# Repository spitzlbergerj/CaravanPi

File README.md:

# CaravanPi

ACHTUNG: Dokumentation nicht aktuell v2.0 noch nicht eingearbeitet

- [Website](https://www.CaravanPi.de)
- [Wiki](https://github.com/spitzlbergerj/CaravanPi/wiki/)
- [Platine bestellen](https://www.caravanpi.de/platine)

- [Newsletter abonnieren (Sendinblue/Brevo Plattform)](https://40fb016c.sibforms.com/serve/MUIFAH4-cq2k2-T8acJ-A43b4eFEC9NdXuY4Qsx0Z8AVap96J-xUTzrsRBFXvzXRIEBnFebbvgbXibn9NFGg8v5Qx55c4hzOQlpmxT23eU7bOGsW2ycUFhNx8PIrJcuGtE8EaE4Ah49gLuzYuZXHCerz-JhMHt5MQxiBJ0xqzuM7EOsEn82apHaTXQg5AoC__NkGssehrymHcnL7)

- [Movitation](#motivation)

## Aktualisierungen / Change Log

Details siehe / Please view [CHANGELOG.md](https://github.com/spitzlbergerj/CaravanPi/blob/master/CHANGELOG.md)

## Motivation

System zur Messung und Anzeige verschiedener Sensorenwerte in Wohnwagen, Caravans und Wohnmobilen, wie z.B. Klimawerte, Füllstände von Tanks und Gasflaschen sowie Nivellierungsdaten. Zur Darstellung wird die Software <a href="https://magicmirror.builders/">Magic Mirror</a> verwendet. 
Es existiert eine Schritt für Schritt Anleitung in deutsch. Englische Schnipsel sind bereits vorhanden und werden ausgebaut werden.
[direkt zur Anleitung](https://github.com/spitzlbergerj/CaravanPi/wiki/Home/)

Schemazeichnung | MagicMirror Anzeige (vor Grafana)
----- | -----
 | 
[größeres Bild](https://github.com/spitzlbergerj/CaravanPi/raw/master/images/CaravanPi.jpg) | [größeres Bild](https://github.com/spitzlbergerj/CaravanPi/raw/master/images/CaravanPi-MagicMirror.jpg) 

## Platinen Design

Die Platine liegt inzwischen in der version V6 vor in die wiederum eine Reihe von Verbesserungen eingeflossen sind.  
Vorderseite | Rückseite
----- | -----
 |  
Alle zum Bestellen der Platine benötigten Angaben und Dateien befinden sich im Verzeichnis circuit-board
Die Platine ist aus SMD Bauteilen aufgebaut. Als Klemmen verwendete ich früher WAGO Klemmen. Aufgrund des hohen Preises derselben bin ich inzwischen auf JST XA Stecker umgestiegen, die auch sehr viel flexibler beim Umbau sind. Bitte auf hochwertige Stecker achten, am besten original JST bauteile verwenden.
Ich kläre gerade mit JLCPCB, bei denen ich meine Platinen bestelle, ob diese Klemmen ebenfalls ab Werk aufgelötet werden können.

Ich habe beinahe immer einige Platinen vorrätig. Bitte nutzen Sie den Bestelllink oben, falls Sie Interesse an einer Platine haben.

## Dokumentation

Die Dokumentation findet im [Wiki](https://github.com/spitzlbergerj/CaravanPi/wiki/) statt. Dieses wird gerade neu aufgebaut, um auch alle neuen Funktionälitäten darstellen zu können.

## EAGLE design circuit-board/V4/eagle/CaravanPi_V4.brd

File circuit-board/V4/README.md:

# Platine Version 4

Diese Platinen Version nutzt SMD Bauteile für alle Widerstände, Kondensatoren, Dioden und ICs inkl. P82B715P I2C Extender Chips. Damit kann diese Platinenversion z. B. bei JLCPCB vollständig gefertigt werden, so dass nur noch Stecker und Klemmen manuell gelötet werden müssen.

## Platinen Layout
Oberseite  

Unterseite  

Bestückungslayout  

Bohrungen  

## JLCPCB Platine maschinell bestückt

Alle für die Bestellung bei JLCPCB.com benötigten dateien finden Sie im Unterverzeichnis [JLCPCB](JLCPCB)

## Bauteile Liste
In der Exceltabelle finden Sie alle benötigten Bauteile

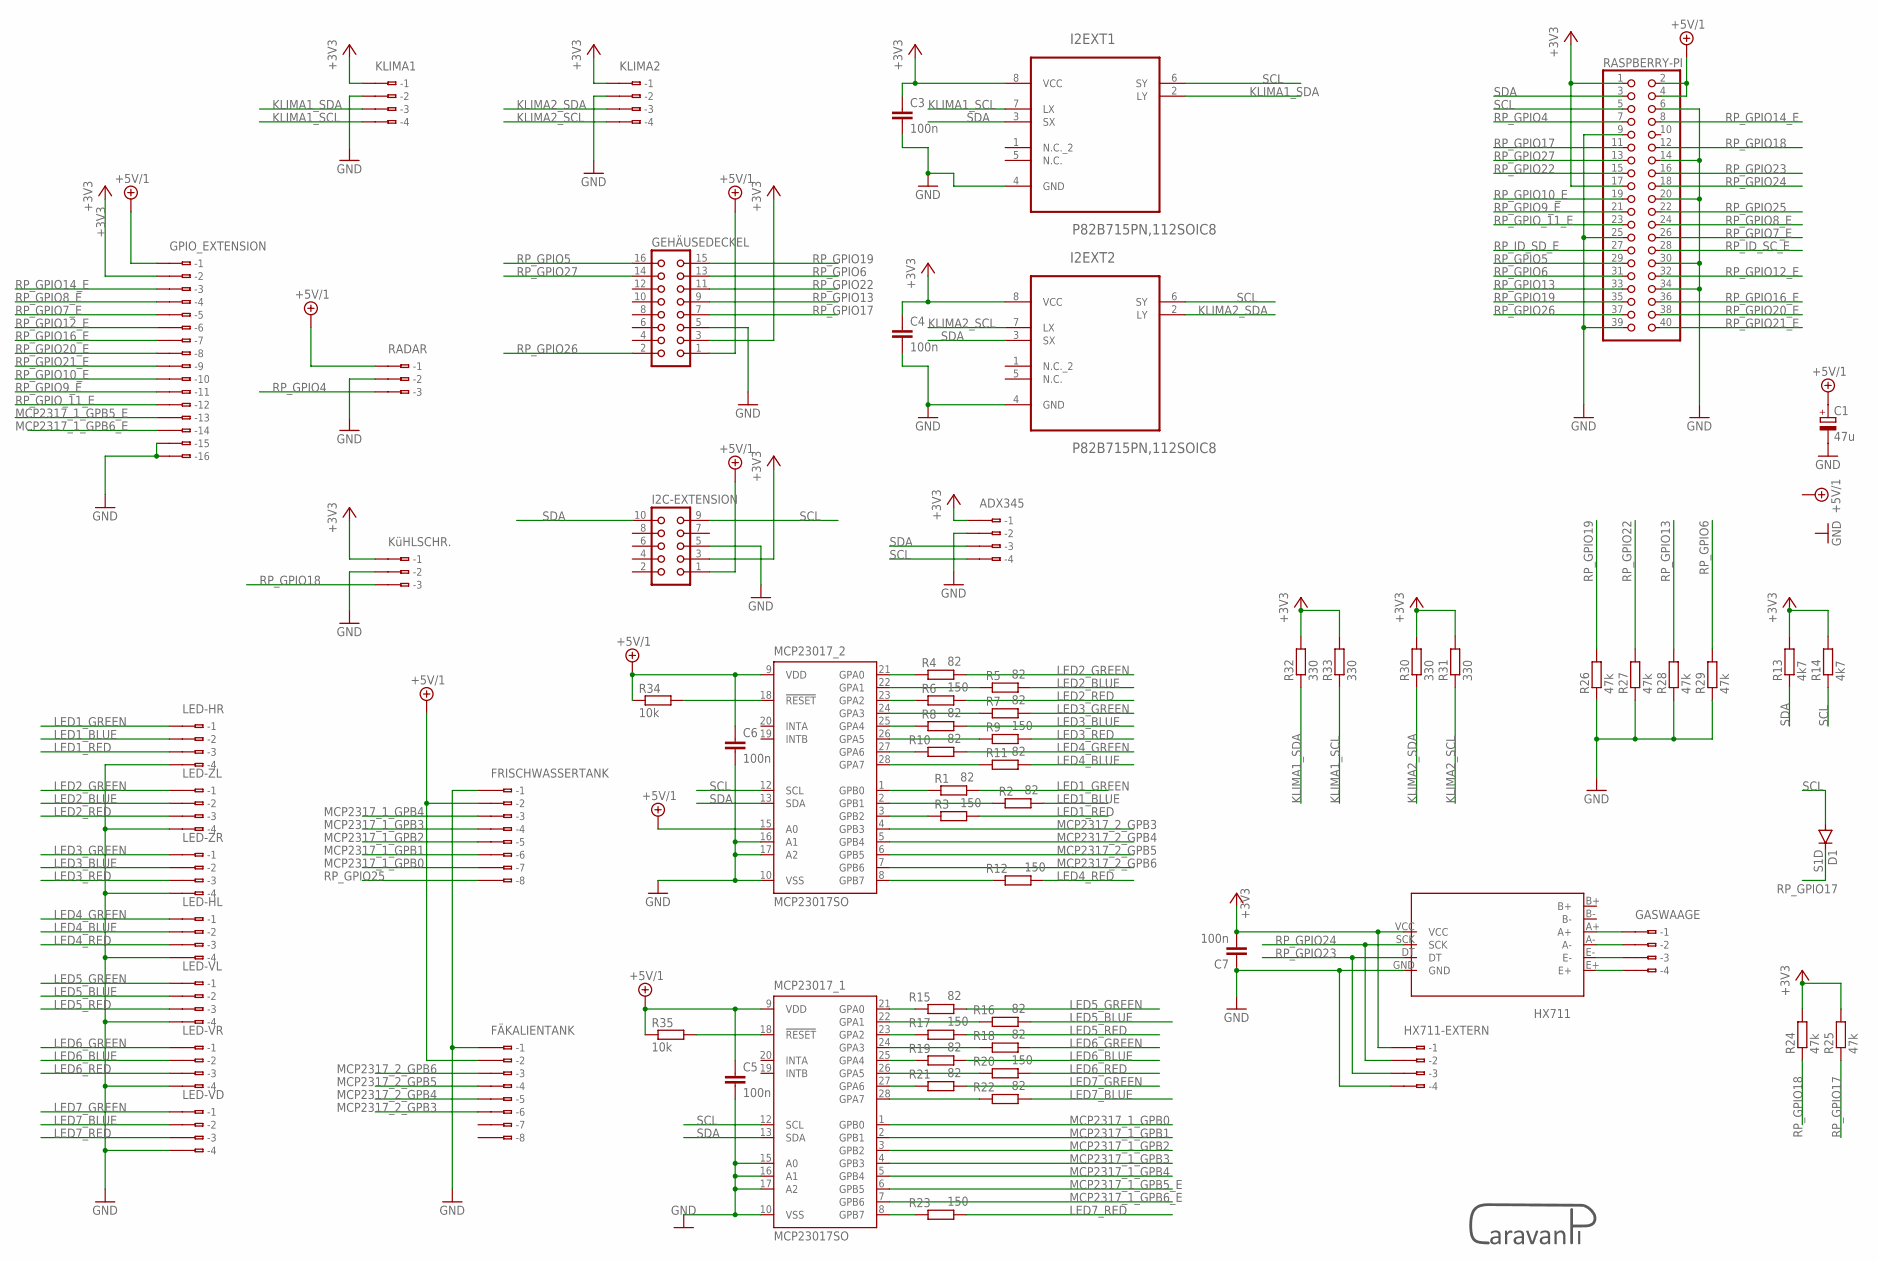
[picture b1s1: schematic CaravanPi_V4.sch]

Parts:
ADX345: 233-404
C1: 47u; SMC_C
C3, C4, C5, C6, C7: 100n; C1206
D1: S1D; DO214AC
FRISCHWASSERTANK: 233-408
FÄKALIENTANK: 233-408
GASWAAGE: 233-404
GEHÄUSEDECKEL: CON16
GPIO_EXTENSION: 233-516
HX711: HX711A; HX711
HX711-EXTERN: 233-404
I2C-EXTENSION: CON10
I2EXT1, I2EXT2: P82B715PN,112SOIC8; SOP127P600X175-8N
KLIMA1, KLIMA2: 233-404
KüHLSCHR.: 233-403
LED-HL: 233-504
LED-HR: 233-504
LED-VD: 233-504
LED-VL: 233-504
LED-VR: 233-504
LED-ZL: 233-504
LED-ZR: 233-504
MCP23017_1, MCP23017_2: MCP23017SO; SO28W
R1, R2, R4, R5, R7, R8, R10, R11, R15, R16, R18, R19, R21, R22: 82; M1206
R3, R6, R9, R12, R17, R20, R23: 150; M1206
R13, R14: 4k7; M1206
R24, R25, R26, R27, R28, R29: 47k; M1206
R30, R31, R32, R33: 330; M1206
R34, R35: 10k; M1206
RADAR: 233-403
RASPBERRY-PI: PINHD-2X20; 2X20
U$1: CARAVAN_PI_LOGO

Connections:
+3V3: ADX345.B1 (B-1), C3.1, C4.1, C7.2, GEHÄUSEDECKEL.3, GPIO_EXTENSION.B2 (B-2), HX711.VCC, HX711-EXTERN.B1 (B-1), I2C-EXTENSION.3, I2EXT1.8 (VCC), I2EXT2.8 (VCC), KLIMA1.B1 (B-1), KLIMA2.B1 (B-1), KüHLSCHR..B1 (B-1), R13.2, R14.2, R24.2, R25.2, R30.2, R31.2, R32.2, R33.2, RASPBERRY-PI.1, RASPBERRY-PI.17
+5V/1: C1.+, C5.1, C6.1, FRISCHWASSERTANK.B2 (B-2), FÄKALIENTANK.B2 (B-2), GEHÄUSEDECKEL.1, GPIO_EXTENSION.B1 (B-1), I2C-EXTENSION.1, MCP23017_1.9 (VDD), MCP23017_2.9 (VDD), MCP23017_2.15 (A0), R34.1, R35.1, RADAR.B1 (B-1), RASPBERRY-PI.2, RASPBERRY-PI.4
GND: ADX345.B2 (B-2), C1.-, C3.2, C4.2, C5.2, C6.2, C7.1, FRISCHWASSERTANK.B1 (B-1), FÄKALIENTANK.B1 (B-1), GEHÄUSEDECKEL.5, GPIO_EXTENSION.B15 (B-15), GPIO_EXTENSION.B16 (B-16), HX711.GND, HX711-EXTERN.B4 (B-4), I2C-EXTENSION.5, I2EXT1.4 (GND), I2EXT2.4 (GND), KLIMA1.B2 (B-2), KLIMA2.B2 (B-2), KüHLSCHR..B2 (B-2), LED-HL.B4 (B-4), LED-HR.B4 (B-4), LED-VD.B4 (B-4), LED-VL.B4 (B-4), LED-VR.B4 (B-4), LED-ZL.B4 (B-4), LED-ZR.B4 (B-4), MCP23017_1.10 (VSS), MCP23017_1.15 (A0), MCP23017_1.16 (A1), MCP23017_1.17 (A2), MCP23017_2.10 (VSS), MCP23017_2.16 (A1), MCP23017_2.17 (A2), R26.1, R27.1, R28.1, R29.1, RADAR.B2 (B-2), RASPBERRY-PI.6, RASPBERRY-PI.9, RASPBERRY-PI.14, RASPBERRY-PI.20, RASPBERRY-PI.25, RASPBERRY-PI.30, RASPBERRY-PI.34, RASPBERRY-PI.39
KLIMA1_SCL: I2EXT1.7 (LX), KLIMA1.B4 (B-4), R33.1
KLIMA1_SDA: I2EXT1.2 (LY), KLIMA1.B3 (B-3), R32.1
KLIMA2_SCL: I2EXT2.7 (LX), KLIMA2.B4 (B-4), R31.1
KLIMA2_SDA: I2EXT2.2 (LY), KLIMA2.B3 (B-3), R30.1
LED1_BLUE: LED-HR.B2 (B-2), R2.2
LED1_GREEN: LED-HR.B1 (B-1), R1.2
LED1_RED: LED-HR.B3 (B-3), R3.2
LED2_BLUE: LED-ZL.B2 (B-2), R5.2
LED2_GREEN: LED-ZL.B1 (B-1), R4.2
LED2_RED: LED-ZL.B3 (B-3), R6.2
LED3_BLUE: LED-ZR.B2 (B-2), R8.2
LED3_GREEN: LED-ZR.B1 (B-1), R7.2
LED3_RED: LED-ZR.B3 (B-3), R9.2
LED4_BLUE: LED-HL.B2 (B-2), R11.2
LED4_GREEN: LED-HL.B1 (B-1), R10.2
LED4_RED: LED-HL.B3 (B-3), R12.2
LED5_BLUE: LED-VL.B2 (B-2), R16.2
LED5_GREEN: LED-VL.B1 (B-1), R15.2
LED5_RED: LED-VL.B3 (B-3), R17.2
LED6_BLUE: LED-VR.B2 (B-2), R19.2
LED6_GREEN: LED-VR.B1 (B-1), R18.2
LED6_RED: LED-VR.B3 (B-3), R20.2
LED7_BLUE: LED-VD.B2 (B-2), R22.2
LED7_GREEN: LED-VD.B1 (B-1), R21.2
LED7_RED: LED-VD.B3 (B-3), R23.2
MCP2317_1_GPB0: FRISCHWASSERTANK.B7 (B-7), MCP23017_1.1 (GPB0)
MCP2317_1_GPB1: FRISCHWASSERTANK.B6 (B-6), MCP23017_1.2 (GPB1)
MCP2317_1_GPB2: FRISCHWASSERTANK.B5 (B-5), MCP23017_1.3 (GPB2)
MCP2317_1_GPB3: FRISCHWASSERTANK.B4 (B-4), MCP23017_1.4 (GPB3)
MCP2317_1_GPB4: FRISCHWASSERTANK.B3 (B-3), MCP23017_1.5 (GPB4)
MCP2317_1_GPB5_E: GPIO_EXTENSION.B13 (B-13), MCP23017_1.6 (GPB5)
MCP2317_1_GPB6_E: GPIO_EXTENSION.B14 (B-14), MCP23017_1.7 (GPB6)
MCP2317_2_GPB3: FÄKALIENTANK.B6 (B-6), MCP23017_2.4 (GPB3)
MCP2317_2_GPB4: FÄKALIENTANK.B5 (B-5), MCP23017_2.5 (GPB4)
MCP2317_2_GPB5: FÄKALIENTANK.B4 (B-4), MCP23017_2.6 (GPB5)
MCP2317_2_GPB6: FÄKALIENTANK.B3 (B-3), MCP23017_2.7 (GPB6)
unnamed: MCP23017_2.1 (GPB0), R1.1
unnamed: MCP23017_2.2 (GPB1), R2.1
unnamed: MCP23017_2.3 (GPB2), R3.1
unnamed: MCP23017_2.21 (GPA0), R4.1
unnamed: MCP23017_2.22 (GPA1), R5.1
unnamed: MCP23017_2.23 (GPA2), R6.1
unnamed: MCP23017_2.24 (GPA3), R7.1
unnamed: MCP23017_2.25 (GPA4), R8.1
unnamed: MCP23017_2.26 (GPA5), R9.1
unnamed: MCP23017_2.27 (GPA6), R10.1
unnamed: MCP23017_2.28 (GPA7), R11.1
unnamed: MCP23017_2.8 (GPB7), R12.1
unnamed: MCP23017_1.21 (GPA0), R15.1
unnamed: MCP23017_1.22 (GPA1), R16.1
unnamed: MCP23017_1.23 (GPA2), R17.1
unnamed: MCP23017_1.24 (GPA3), R18.1
unnamed: MCP23017_1.25 (GPA4), R19.1
unnamed: MCP23017_1.26 (GPA5), R20.1
unnamed: MCP23017_1.27 (GPA6), R21.1
unnamed: MCP23017_1.28 (GPA7), R22.1
unnamed: MCP23017_2.18 (!RESET), R34.2
unnamed: MCP23017_1.18 (!RESET), R35.2
unnamed: GASWAAGE.B4 (B-4), HX711.E+
unnamed: GASWAAGE.B3 (B-3), HX711.E-
unnamed: GASWAAGE.B2 (B-2), HX711.A-
unnamed: GASWAAGE.B1 (B-1), HX711.A+
unnamed: MCP23017_1.8 (GPB7), R23.1
RP_GPIO4: RADAR.B3 (B-3), RASPBERRY-PI.7
RP_GPIO5: GEHÄUSEDECKEL.16, RASPBERRY-PI.29
RP_GPIO6: GEHÄUSEDECKEL.13, R29.2, RASPBERRY-PI.31
RP_GPIO7_E: GPIO_EXTENSION.B5 (B-5), RASPBERRY-PI.26
RP_GPIO8_E: GPIO_EXTENSION.B4 (B-4), RASPBERRY-PI.24
RP_GPIO9_E: GPIO_EXTENSION.B11 (B-11), RASPBERRY-PI.21
RP_GPIO10_E: GPIO_EXTENSION.B10 (B-10), RASPBERRY-PI.19
RP_GPIO12_E: GPIO_EXTENSION.B6 (B-6), RASPBERRY-PI.32
RP_GPIO13: GEHÄUSEDECKEL.9, R28.2, RASPBERRY-PI.33
RP_GPIO14_E: GPIO_EXTENSION.B3 (B-3), RASPBERRY-PI.8
RP_GPIO16_E: GPIO_EXTENSION.B7 (B-7), RASPBERRY-PI.36
RP_GPIO17: D1.C, GEHÄUSEDECKEL.7, R25.1, RASPBERRY-PI.11
RP_GPIO18: KüHLSCHR..B3 (B-3), R24.1, RASPBERRY-PI.12
RP_GPIO19: GEHÄUSEDECKEL.15, R26.2, RASPBERRY-PI.35
RP_GPIO20_E: GPIO_EXTENSION.B8 (B-8), RASPBERRY-PI.38
RP_GPIO21_E: GPIO_EXTENSION.B9 (B-9), RASPBERRY-PI.40
RP_GPIO22: GEHÄUSEDECKEL.11, R27.2, RASPBERRY-PI.15
RP_GPIO23: HX711.DT, HX711-EXTERN.B3 (B-3), RASPBERRY-PI.16
RP_GPIO24: HX711.SCK, HX711-EXTERN.B2 (B-2), RASPBERRY-PI.18
RP_GPIO25: FRISCHWASSERTANK.B8 (B-8), RASPBERRY-PI.22
RP_GPIO26: GEHÄUSEDECKEL.2, RASPBERRY-PI.37
RP_GPIO27: GEHÄUSEDECKEL.14, RASPBERRY-PI.13
RP_GPIO_11_E: GPIO_EXTENSION.B12 (B-12), RASPBERRY-PI.23
RP_ID_SC_E: RASPBERRY-PI.28
RP_ID_SD_E: RASPBERRY-PI.27
SCL: ADX345.B4 (B-4), D1.A, I2C-EXTENSION.9, I2EXT1.6 (SY), I2EXT2.6 (SY), MCP23017_1.12 (SCL), MCP23017_2.12 (SCL), R14.1, RASPBERRY-PI.5
SDA: ADX345.B3 (B-3), I2C-EXTENSION.10, I2EXT1.3 (SX), I2EXT2.3 (SX), MCP23017_1.13 (SDA), MCP23017_2.13 (SDA), R13.1, RASPBERRY-PI.3

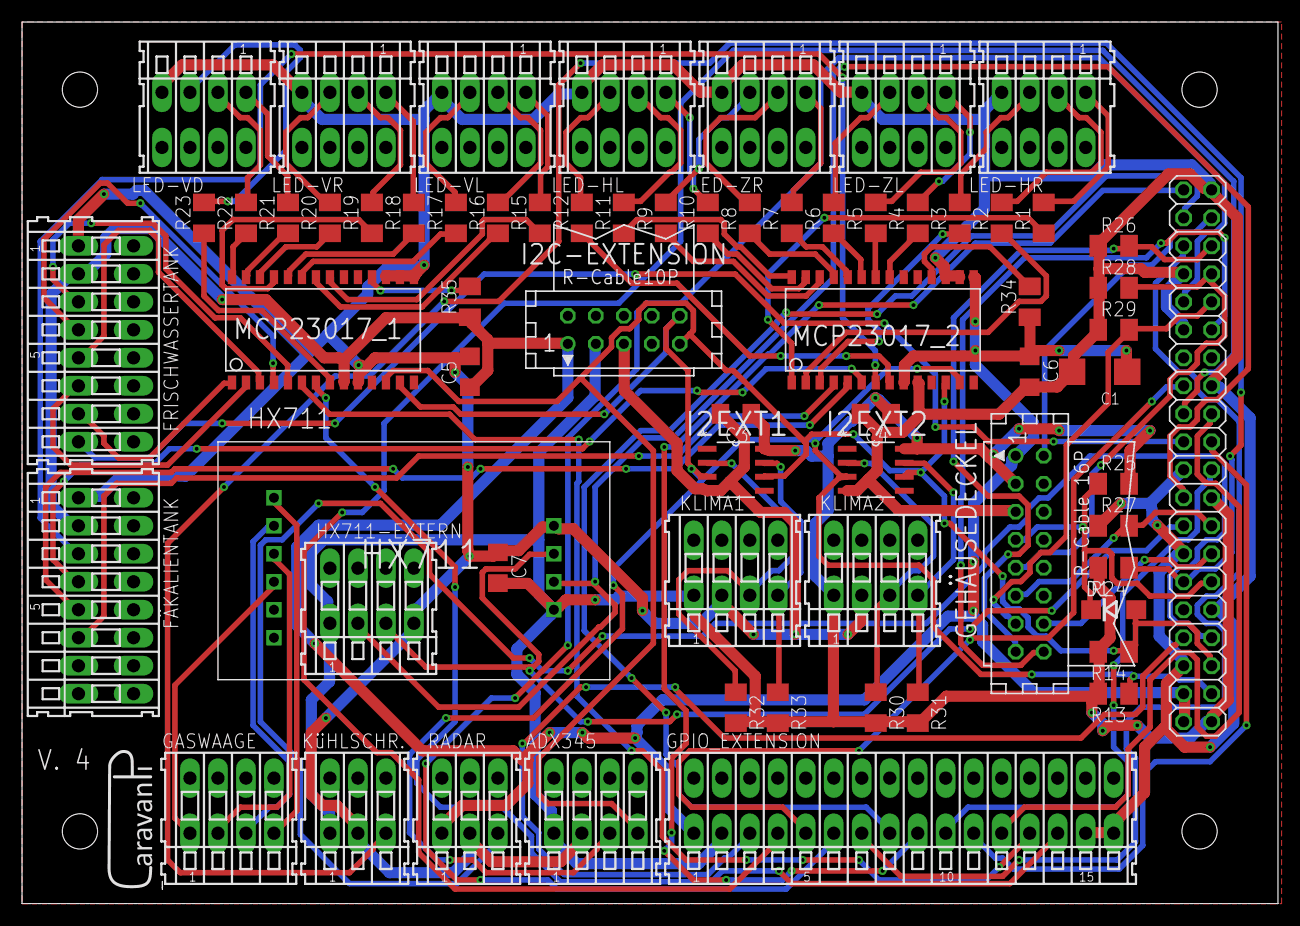
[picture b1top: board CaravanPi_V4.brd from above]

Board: 2 copper layers, 114.0 x 80.0 mm, 68 parts (0 on the bottom side), 91 nets.

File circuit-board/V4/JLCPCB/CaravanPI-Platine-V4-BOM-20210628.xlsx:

Comment | Designator | Footprint | LCSC Part #（optional）
100n | C3, C4, C5, C6, C7 | C1206 | C24497
10k | R34, R35 | M1206 | C17902
82 GRUEN | R1,R4,R7,R10,R15,R18,R21 | M1206 | C17980
82 BLAU | R2,R5,R8,R11,R16,R19,R22 | M1206 | C17980
150 ROT | R3,R6,R9,R12,R17,R20,R23 | M1206 | C17917
330 | R30, R31, R32, R33 | M1206 | C17930
47k | R24, R25, R26, R27, R28, R29 | M1206 | C25833
47u | C1 | SMC_C | C123258
4k7 | R13, R14 | M1206 | C242482
MCP23017SO | MCP23017_1, MCP23017_2 | SOIC-28_300mil | C47023
P82B715PN,112SOIC8 | I2EXT1, I2EXT2
S1D | D1 | DO214AC | C154769

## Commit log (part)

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2020-08-28 diverse Korrekturen
2020-08-29 Änderung Pfade für Dokumentations Images
2020-08-29 Changed LED Pin to BCM27
    Changed from BCM21 to BCM27
    all Pins for the operate panel to the GPIO odd side
2020-08-29 Changed Pins
    tactile switch calibration gasscale pin changed from BCM24 to BCM22
    tactile switch calibration position sensor pin changed from BCM23 to BCM 19
    all Pins for the operate panel to the GPIO odd side
2020-08-29 Changed pins
    tactile switch calibration gasscale pin changed from BCM24 to BCM22
    tactile switch calibration position sensor pin changed from BCM23 to BCM 19
    tactile switch to set the current position in transverse direction as horizontal pin changed from BCM12 to BCM6
    LED live Mode pin changed from BCM16 to BCM5
    all Pins for the operate panel to the GPIO odd side
2020-08-29 changed pins
    tactile switch to set the current position in transverse direction as horizontal pin changed from BCM12 to BCM6
    LED live Mode pin changed from BCM16 to BCM5
    all Pins for the operate panel to the GPIO odd side
2020-08-29 changed pir pin
    pir data pin changed from BCM25 to BCM4
    all Pins for the operate panel to the GPIO odd side
2020-08-29 pins changed
    HX711 pins changed from BCM5 to BCM23 and from BCM6 to BCM24
    all Pins for the operate panel to the GPIO odd side al other to the other side
2020-08-30 erste Version levels2file.py
2020-09-06 PIR Sensor am Testgerät auslesen
    PIR Sensor mit den Testgerät (Raspberry Pi mit Testaufsatz) testen und optimalen Einbauort finden
2020-09-27 diverse Anpassungen, Verbesserungen und Fehlerkorrekturen sowie Einbau Tank Füllstände
2020-09-30 Backup und logrotate aktiviert
2020-10-05 levels of freshwater and waste water separated
2020-10-10 License changed to AGPL
    This project, as well as all modifications, extensions, ..., should remain open and usable for everyone at any time. Commercial use cannot be excluded, but through the AGPL all these developments and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
2020-10-10 Fäkalientank Programme
2020-10-16 BME680 eingefügt - noch unfertig
2020-10-23 Lösung für issue One-Digit-Temperature
    Umstellung der Formatierung des Temperaturwerts in Zeile 44 sowie Anpassung der Aufbereitung beim Schrieben in die Datei (Einfügen eines Spaces)
2020-11-03 Integration of BME680 sensor (work in progress) and other improvements
2021-03-25 Platinenlayout Version 03/2021
2021-05-13 Frischwassertank Testaufbau
2021-05-13 update of level description in fresh water tank
2021-05-13 Rename circuit/Readme.md to circuit-board/Readme.md
2021-05-13 Rename circuit/eagle/Readme.md to circuit-board/eagle/Readme.md
2021-05-13 Rename circuit/gerber/Readme.md to circuit-board/gerber/Readme.md
2021-05-13 Upload all files to order a circuit board
2021-05-13 circuit to circuit-board
2021-05-13 Fäkalientank Testaufbau
2021-05-14 circuit board Version 3 gerber files
    The circuit board version 2 is faulty. The connection for the radar sensor must be supplied with 5V instead of 3.3V. The circuit board version 3 fixes this error
2021-05-14 Delete profile.gbr
    The circuit board version 2 is faulty. The connection for the radar sensor must be supplied with 5V instead of 3.3V. The circuit board version 3 fixes this error
2021-05-14 Delete silkscreen_bottom.gbr
    The circuit board version 2 is faulty. The connection for the radar sensor must be supplied with 5V instead of 3.3V. The circuit board version 3 fixes this error
2021-05-14 Delete silkscreen_top.gbr
    The circuit board version 2 is faulty. The connection for the radar sensor must be supplied with 5V instead of 3.3V. The circuit board version 3 fixes this error
2021-05-14 Delete solderpaste_bottom.gbr
    The circuit board version 2 is faulty. The connection for the radar sensor must be supplied with 5V instead of 3.3V. The circuit board version 3 fixes this error
2021-05-14 circuit board version 3
    The circuit board version 2 is faulty. The connection for the radar sensor must be supplied with 5V instead of 3.3V. The circuit board version 3 fixes this error
2021-05-14 circuit board version 2 is faulty
    The circuit board version 2 is faulty. The connection for the radar sensor must be supplied with 5V instead of 3.3V. The circuit board version 3 fixes this error
2021-05-14 circuit board version 2 is faulty --> version 3
    The circuit board version 2 is faulty. The connection for the radar sensor must be supplied with 5V instead of 3.3V. The circuit board version 3 fixes this error
2021-05-14 circuit board version 2 is faulty
2021-05-15 gerber files als zip
2021-05-15 gerber only as zip file necessary
2021-05-21 circuit board mearurements
2021-05-24 3D Druck Modelle
2021-06-01 Halterungen für die Reed Kontakte am Fäkalientank
2021-06-01 FreeCAD File für Reed Kontakte Halterung
    Diese Konstruktion ist voll parametrisch und kann über ein FreeCAD Spreadsheet individuell angepasst werden.
2021-06-01 Reed Kontakte Halterungen
2021-06-04 more 3D Parts
2021-06-13 Bestellprozess Platine
2021-06-24 circuit board, SMT assembled, from JLCPCB has arrived
2021-06-25 creation of subdirectories at circuit board
    Version 3 - first finale Version for external circuit board production with P82B175B as THT (through hole technology) device
    Version 4 - P82B175B as SMD (surface-mounted device)
2021-06-26 correction preview image condensator C1 polarisation
2021-06-28 JLCPCB Files added
    Problem: cann't find a SMD version of the P82B715P
2021-07-17 LED connectors synchronized with circuit board
2021-12-29 resistor id changed because original one was out of stock
2022-04-26 V 1.09a mehrere Gaswaagen, Waagen-Kalibrierung neu, kleine Korrekturen
2022-04-26 V 1.09b mehrere Gaswaagen, Waagen-Kalibrierung neu, kleine Korrekturen
2022-04-28 V5 der CaravanPi Platine
    - reine SMD Platine, keine bedrahteten Bauteile mehr
    - Fehlerkorrektur beim Widerstand R24 - 1-wire-Bus, nun 4k7 anstatt fälschlicherweise 47k
    - Gaswaagen-Klemme nun 6 Polig, um A und B Kanal des HX711 auf Klemmen zu führen
2022-04-28 Erweiterung um V5 Platine
2022-09-01 gasScale2file.py now with argument -g <nr>
    Support of more than one gasscale
2022-09-01 diverse Anpassungen des default config.js aufgrund Änderungen in der MagicMirror SW
2023-01-08 Einführung einer Konfigurationsdatei für CaravanPi allgemein
    Angabe von z.B. Anzahl Gaswaagen oder Anzahl Tanks.
    späterer weiterer Ausbau geplant
2023-01-08 Einführung einer Konfigurationsdatei für CaravanPi allgemein
2023-01-08 Update gasScaleDefaults1
2023-01-08 Update gasScaleDefaults2
2023-01-08 Einführung mehrerer Gaswaagen
    Schreiben der Files mit einer Gaswaagen Nummer
2023-01-08 Korrektur der falschen Kalibrierung der Gaswaagen
    Einführung mehrerer Gaswaagen auch in der Kalibrierung
    Korrektur der falschen Kalibrierungsweise in der HTML Oberfläche
    Aufnahme der GPIO Parameter für die Steuerung der Gaswaagen Abfrage und die Ansteuerung der HX711 über diese Parameter
2023-02-23 V5 Gerber-File, BOM-File, CPL-File
2023-02-23 part list and placement images
2023-04-11 BOM file updated,part placement image
    BOM file updated due to part outage at JLCPPCB
    additional image with the correct parts placement
2023-05-02 CaravanPi Platine Verkabelung zum Raspberry Pi
2023-07-29 CaravanPi Platine V5 Front Back
2023-12-29 Specifications LED
2023-12-31 Schreiben in MariaDB, senden an MQTT Broker, Systemzustände
    Die CaravanPiFilesClass wurde ergänzt um Funktionen zum Schreiben in eine mariaDB und zum Senden an einen MQTT Broker. Die zugehören Anmeldedaten werden aus der Config-xml gelesen. Im Verzeichnis ras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
2024-01-02 zentrale Sensorwert Verarbeitung (File,DB,MQTT)
    in der CaravnPiFiles Class wurde eine zentrale Funktion geschaffen, die zukünftig alle Schreib Vorgänge für Sensorwerte übernimmt. Die Funktion gibt am Bildschirm aus, schreibt die Werte in ein File,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
2024-01-02 Fehlerzustände
    Fehlerzustände werden nun mit ERROR oder WARNING deutlich in den Bildschirmausgaben bzw. Logdaten Einträgen markiert
2024-01-02 dokumentstion ergänzt
2024-01-02 behandlung von sensiblen Daten
    um Passworte etc, die z.B. in der xml Datei in meiner Entwiclungsumgebung vorhanden sind, nicht auf github hochzuladen, habe ich git hooks angelegt
2024-01-02 testcommit
2024-01-06 diverse Änderungen, Flask Websites
    weitere Härtung einiger pythonskripte, weiterer Aufbau der Flask Websites als Ersatz für die bisherigen Websites
2024-02-18 weitere Seiten für Config, Calibration, usw. in Flask
    Die Defaults Datei wurde an einigen Stellen erweitert, damit auch die librarys. In Flask wurde die Checks erweitert um crontab und Netzwerk. Die Konfiguration von Defaults, Gaswaagen Lagensensor, Tan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
2024-03-02 flask website weiterentwickelt, configs weiterentwickelt, 230V Check, Gas Check, BatteryMgmt Liontron
    Die Flask Webseite wurde um Test Routinen, weiter Configs und Checks erweitert. Die Gaswaagen wurden getestet, aber sind noch nicht fertig. Die mariaDB wird nun bereinigt. Ein AD Wandler wurde integr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
2024-03-03 git hooks, gassensor-, 230v-, 12v-Checks fertig, flask button menues
    git: Hooks ergänzt, so dass crontabs jeweisl mitgesichert werden; Gassensor, 230V und 12V Check Routinen abgeschlossen; Flask sites: menüs alle auf Buttons umgestellt; Flask sites: Aktoren eingebaut
2024-03-10 Ansteuerung und Datenempfang von externem ESP82 als Aktor
    Die Überwachung von 12V Batterien wurde fertiggestellt. Ein ESP82 D1 mini wurde beispielhaft integriert, um die Interaktion mit Aktoren zu demonstrieren. Dabei wurde am ESP ein Taster und eine LED in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
2024-03-10 Installationsskript vorbereitet / noch nicht fertig
    allererste Version eines Installations- und Updateskriptes für den gesamten CaravanPi angelegt. Das Skript funktioniert noch nicht - NICHT AUSFUEHREN
2024-03-10 Add caravanpiConfig.xml to version control
2024-03-11 defauts angepasst
2024-03-11 Fehlerkorrektor Resume Werte
2024-03-13 Installationsskript bearbeitet
    Installationsskript getestet und schrittweise ergänzt
2024-03-13 Anpassung Installationsskript - Parameter verarbeitung
2024-03-13 Installationsskript erweitert - MagicMirror
2024-03-13 Instsallationsskript erweitert bis inkl. grafana
2024-03-13 korrektur Installtionsskript
2024-03-13 Installationsskript farbige Prompts
2024-03-13 Intallationsskript Fehlerbehebung
2024-03-13 Installationsskrip weiter entwickelt
    Raspberry os, CaravanPi, MagicMirror, MariaDB, phpmyadmin, Grafana, python bibliotheken, Apache, Flask sind schon implemetiert
2024-03-14 Installationsskript weiter entwickelt
2024-03-14 Installationsskript, Flask-Routen angepasst
2024-03-14 Installationsskript korrigiert
2024-03-14 weitere Korrekturen am Install Skript
2024-03-14 Fehlerkorrektur Installationsskript
2024-03-14 Installationsskript optimiert; 230V, 12V Überwachung schreibt in DB
2024-03-14 230V schreibt in DB
2024-03-14 git hook test
2024-03-14 Gassensor,v230 v12 Datenbank Inserts, Flask ohne services
2024-03-15 Library Probleme Adafruit
2024-03-15 Platine V6, StromPi Installtion im Skript, Tank-Routinen aktualisiert, gpiozero in position und Taster eingebaut
2024-03-15 Config durch kalibrierung geändert
2024-03-15 SplashScreen setzen, StromPi3 Skripte, Installationsskript anpassen
2024-03-16 git hooks Config xml standardwerte, Install DB Daten in xml schreiben
2024-03-16 Hintergrund Bild
2024-03-16 kleine Fehlerkorrekturen Flask Routinen
2024-03-16 kleine Fehlerkorrekturen Flask Config Route
2024-03-16 weitere Fehlerkorrekturen
2024-03-16 weitere Fehlerkorrekturen und kleine Erweiterungen
2024-03-16 kleine Fehlerbehebungen und Stabilisierung
2024-03-17 Testdaten generiert für Kühlschrank, Gas und Klima sowie Lage; Import Skript erstellt; Lib angepasst wegen zeitstempel <> now()
2024-03-19 README und CHANGELOG aktualtisiert
2024-03-19 newsletter in das Repository integriert
2024-03-22 Fehlerkorrektur install Skript, Anpassung git hook post-commit
2024-03-27 Newsletter eingefügt; Spannungsteiler-Berechnung erweitert
2024-05-29 Update LICENSE
